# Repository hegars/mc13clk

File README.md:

# mc13clk
 Clock Module I built for a TV production
 
 Uses Arduino Nano v3.0 + EasyDriver v4.5 + MCP23017 i2c expander

## Early prototype

## Version 1

## Version 2.0.0 completed module

## Version 2.0.1 

* Easydrive pins alligined correctly

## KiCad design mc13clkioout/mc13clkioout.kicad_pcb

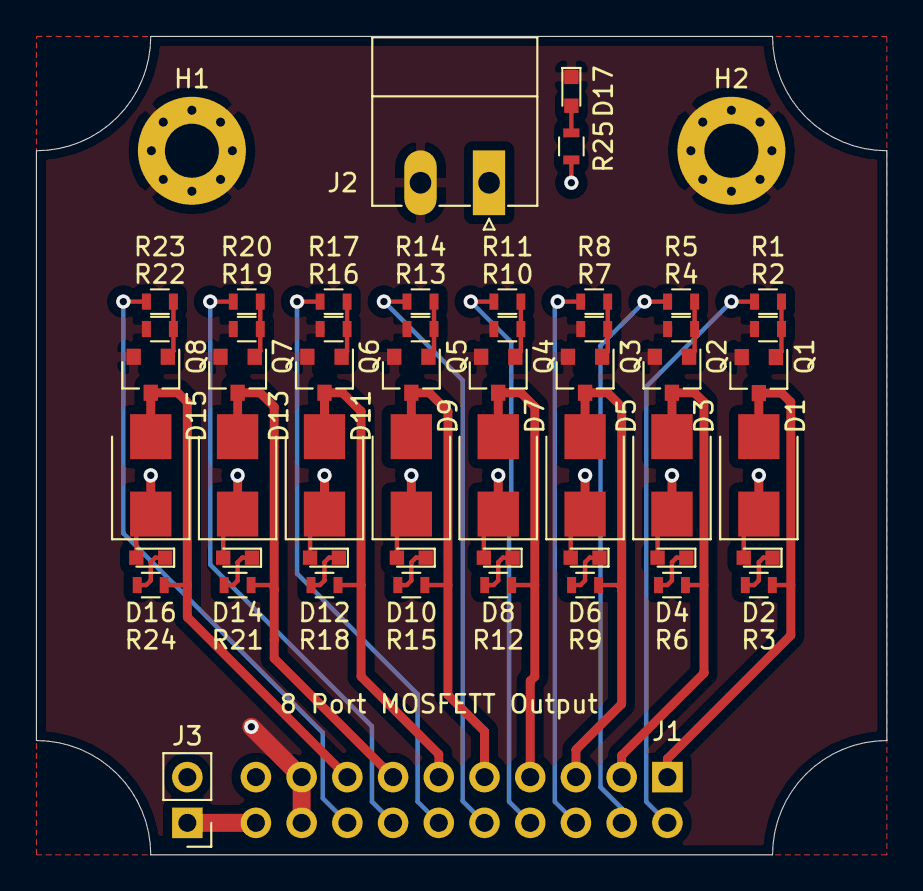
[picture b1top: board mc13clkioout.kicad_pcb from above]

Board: 2 copper layers, 47.2 x 45.5 mm, 55 parts (1 on the bottom side), 36 nets.

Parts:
D1, D3, D5, D7, D9, D11, D13, D15: 1N4004; D_SMB
D2, D4, D6, D8, D10, D12, D14, D16, D17: LED; LED_0603
H1, H2: MountingHole_Pad; MountingHole_3mm_Pad_Via
J1: Conn_02x10_Counter_Clockwise; Socket_Strip_Angled_2x10_Pitch2.54mm
J2: 5-24Vdc; PhoenixContact_MC-G_02x3.81mm_Angled
J3: VBUS Tie; Pin_Header_Straight_1x02_Pitch2.54mm
Q1, Q2, Q3, Q4, Q5, Q6, Q7, Q8: 2N7002; SOT-23
R1, R3, R4, R6, R7, R9, R10, R12, R13, R15, R16, R18, R19, R21, R22, R24: 1K; R_0603
R2, R5, R8, R11, R14, R17, R20, R23: 10K; R_0603
R25: 2K2; R_0603

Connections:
/Input1: J1.2, R1.2
/Input2: J1.4, R4.2
/Input3: J1.6, R7.2
/Input4: J1.8, R10.2
/Input5: J1.10, R13.2
/Input6: J1.12, R16.2
/Input7: J1.14, R19.2
/Input8: J1.16, R22.2
/Output1: D1.2, J1.1, Q1.3, R3.1
/Output2: D3.2, J1.3, Q2.3, R6.1
/Output3: D5.2, J1.5, Q3.3, R9.1
/Output4: D7.2, J1.7, Q4.3, R12.1
/Output5: D9.2, J1.9, Q5.3, R15.1
/Output6: D11.2, J1.11, Q6.3, R18.1
/Output7: D13.2, J1.13, Q7.3, R21.1
/Output8: D15.2, J1.15, Q8.3, R24.1
GND: D17.1, H1.1, H2.1, J1.17, J1.18, J2.2, Q1.2, Q2.2, Q3.2, Q4.2, Q5.2, Q6.2, Q7.2, Q8.2, R2.1, R5.1, R8.1, R11.1, R14.1, R17.1, R20.1, R23.1
unnamed: D2.1, R3.2
unnamed: D4.1, R6.2
unnamed: D6.1, R9.2
unnamed: D8.1, R12.2
unnamed: D10.1, R15.2
unnamed: D12.1, R18.2
unnamed: D14.1, R21.2
unnamed: D16.1, R24.2
unnamed: D17.2, R25.1
unnamed: Q1.1, R1.1, R2.2
unnamed: Q2.1, R4.1, R5.2
unnamed: Q3.1, R7.1, R8.2
unnamed: Q4.1, R10.1, R11.2
unnamed: Q5.1, R13.1, R14.2
unnamed: Q6.1, R16.1, R17.2
unnamed: Q7.1, R19.1, R20.2
unnamed: Q8.1, R22.1, R23.2
VBUS: J1.20, J3.1
VCC: D1.1, D2.2, D3.1, D4.2, D5.1, D6.2, D7.1, D8.2, D9.1, D10.2, D11.1, D12.2, D13.1, D14.2, D15.1, D16.2, J1.19, J2.1, J3.2, R25.2

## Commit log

2021-02-27 updates files
2021-02-27 added complete module
2021-02-27 added proto
2021-02-27 added version 1
2021-02-27 v1rat
